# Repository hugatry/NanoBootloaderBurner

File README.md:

# NanoBootloaderBurner
 Hardware programmer for programming (bootloader to) Arduino Nano compatible development board
 Purpose of this repository is to share the design files for board shown in my YouTube video: [https://youtu.be/Mxi_6IfEGUE](https://youtu.be/Mxi_6IfEGUE)
 
 Holes for the target Nano have been increased to 1.1mm, which should allow using cheap pogo-pins instead of female headers. This modification hasn't been tested yet.
 
 This programmer is ment to be super simple and it works in it's current form. Possible "bug fixes" may be committed at some point, but otherwise this project is considered finished.
 
## Firmware
 For firmware, you can use "ArduinoISP" -example sketch that comes with the Arduino IDE. 
 Pin configuration is following (Can be found around line 75 in example sketch, edit if needed):
 * RESET = 10
 * LED_ERR = 7
 * LED_PMODE = 8
 
 Bare ATMega328p doesn't have bootloader in it from the factory, so you need to use another ISP programmer to program either that ArduinoISP -sketch or Arduino bootloader into the chip. If you decide to program bootloader, you can then use the USB-port to program the actual firmware to the chip. Bootloader method allows updating the firmware via USB-port and external programmer is only needed for initial bootloader programming.
 
## USAGE
 Keep in mind, using any ISP programmer can and will probably erase everything on the microcontroller that is being programmed. This has potential of bricking the microcontroller, making it unusable, unless one has a more expensive programmer to fix it. Use at your own risk.
 
 Once the onboard ATMega328p has the ArduinoISP running, you can use this device to program bootloaders to Arduino Nano -compatible boards using Arduino IDE.
 Make following selections in the Arduino IDE:
 * Tools->Board->Arduino Nano
 * Tools->Processor->ATmega328p (Or ATmega168p, if your Nano has that MCU)
 * Tools->Programmer->"Arduino as ISP"
 * Tools->Port-> The com port of the programmer
 
 Then you can plug the Nano to the programmer, and select Tools->"Burn bootloader" in Arduino IDE to program the fresh bootloader to your Nano.

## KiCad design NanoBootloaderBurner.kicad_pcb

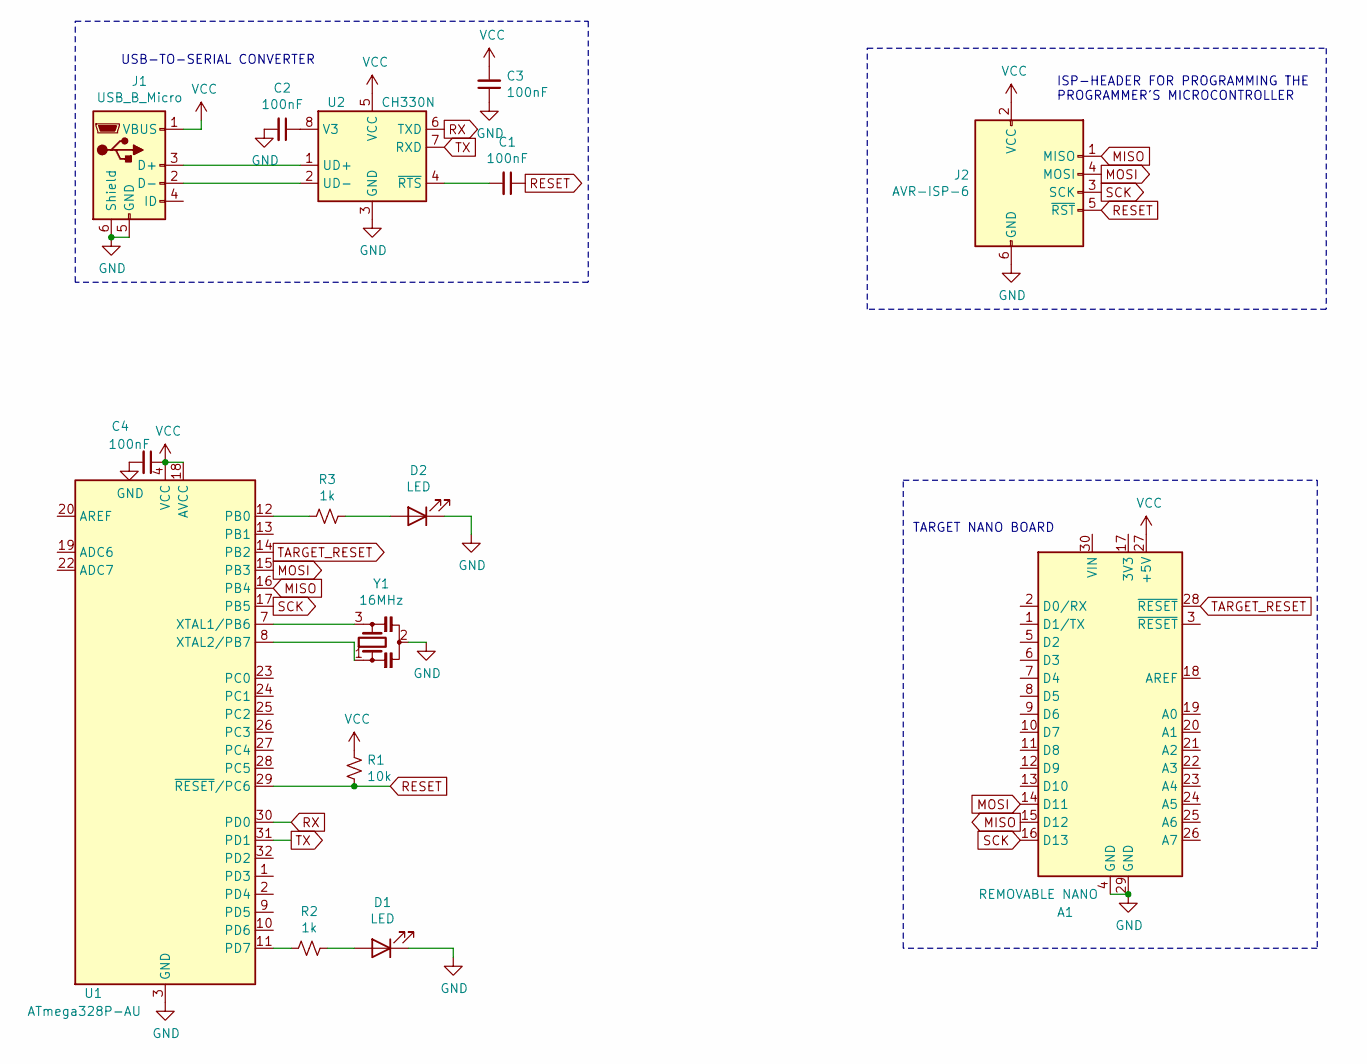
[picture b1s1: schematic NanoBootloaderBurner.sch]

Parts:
A1: REMOVABLE NANO; Arduino_Nano
C1, C2, C3, C4: 100nF; C_0603_1608Metric
D1, D2: LED; LED_D5.0mm
J1: USB_B_Micro; USB_Micro
J2: AVR-ISP-6; PinHeader_2x03_P2.54mm_Vertical
R1: 10k; R_0603_1608Metric
R2, R3: 1k; R_0603_1608Metric
U1: ATmega328P-AU; TQFP-32_7x7mm_P0.8mm
U2: CH330N; SOIC-8_3.9x4.9mm_P1.27mm
Y1: 16MHz; Resonator_SMD_muRata_CSTxExxV-3Pin_3.0x1.1mm

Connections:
GND: A1.4 (GND), A1.29 (GND), C2.2, C3.1, C4.2, D1.1 (K), D2.1 (K), J1.5 (GND), J1.6 (Shield), J2.6 (GND), U1.3 (GND), U1.5 (GND), U1.21 (GND), U2.3 (GND), Y1.2
MISO: A1.15 (D12), J2.1 (MISO), U1.16 (PB4)
MOSI: A1.14 (D11), J2.4 (MOSI), U1.15 (PB3)
unnamed: C1.2, U2.4 (~RTS)
unnamed: C2.1, U2.8 (V3)
unnamed: D1.2 (A), R2.1
unnamed: D2.2 (A), R3.1
unnamed: J1.2 (D-), U2.2 (UD-)
unnamed: J1.3 (D+), U2.1 (UD+)
unnamed: R2.2, U1.11 (PD7)
unnamed: R3.2, U1.12 (PB0)
unnamed: U1.7 (XTAL1/PB6), Y1.3
unnamed: U1.8 (XTAL2/PB7), Y1.1
RESET: C1.1, J2.5 (~RST), R1.2, U1.29 (~RESET~/PC6)
RX: U1.30 (PD0), U2.6 (TXD)
SCK: A1.16 (D13), J2.3 (SCK), U1.17 (PB5)
TARGET_RESET: A1.28 (~RESET), U1.14 (PB2)
TX: U1.31 (PD1), U2.7 (RXD)
VCC: A1.27 (+5V), C3.2, C4.1, J1.1 (VBUS), J2.2 (VCC), R1.1, U1.4 (VCC), U1.6 (VCC), U1.18 (AVCC), U2.5 (VCC)

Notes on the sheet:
ISP-HEADER FOR PROGRAMMING THE PROGRAMMER'S MICROCONTROLLER
TARGET NANO BOARD
USB-TO-SERIAL CONVERTER

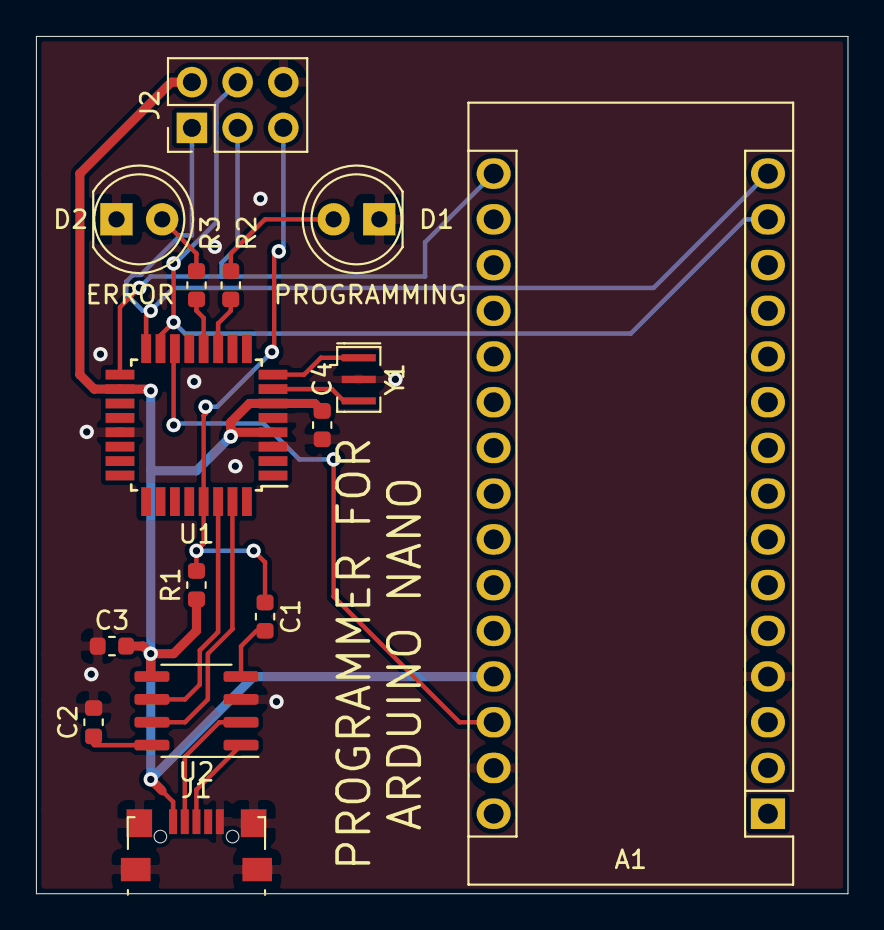
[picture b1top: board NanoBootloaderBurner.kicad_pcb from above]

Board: 2 copper layers, 45.1 x 47.6 mm, 15 parts (0 on the bottom side), 19 nets.
